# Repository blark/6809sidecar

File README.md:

# 6809sidecar

This board is untested and experimental.

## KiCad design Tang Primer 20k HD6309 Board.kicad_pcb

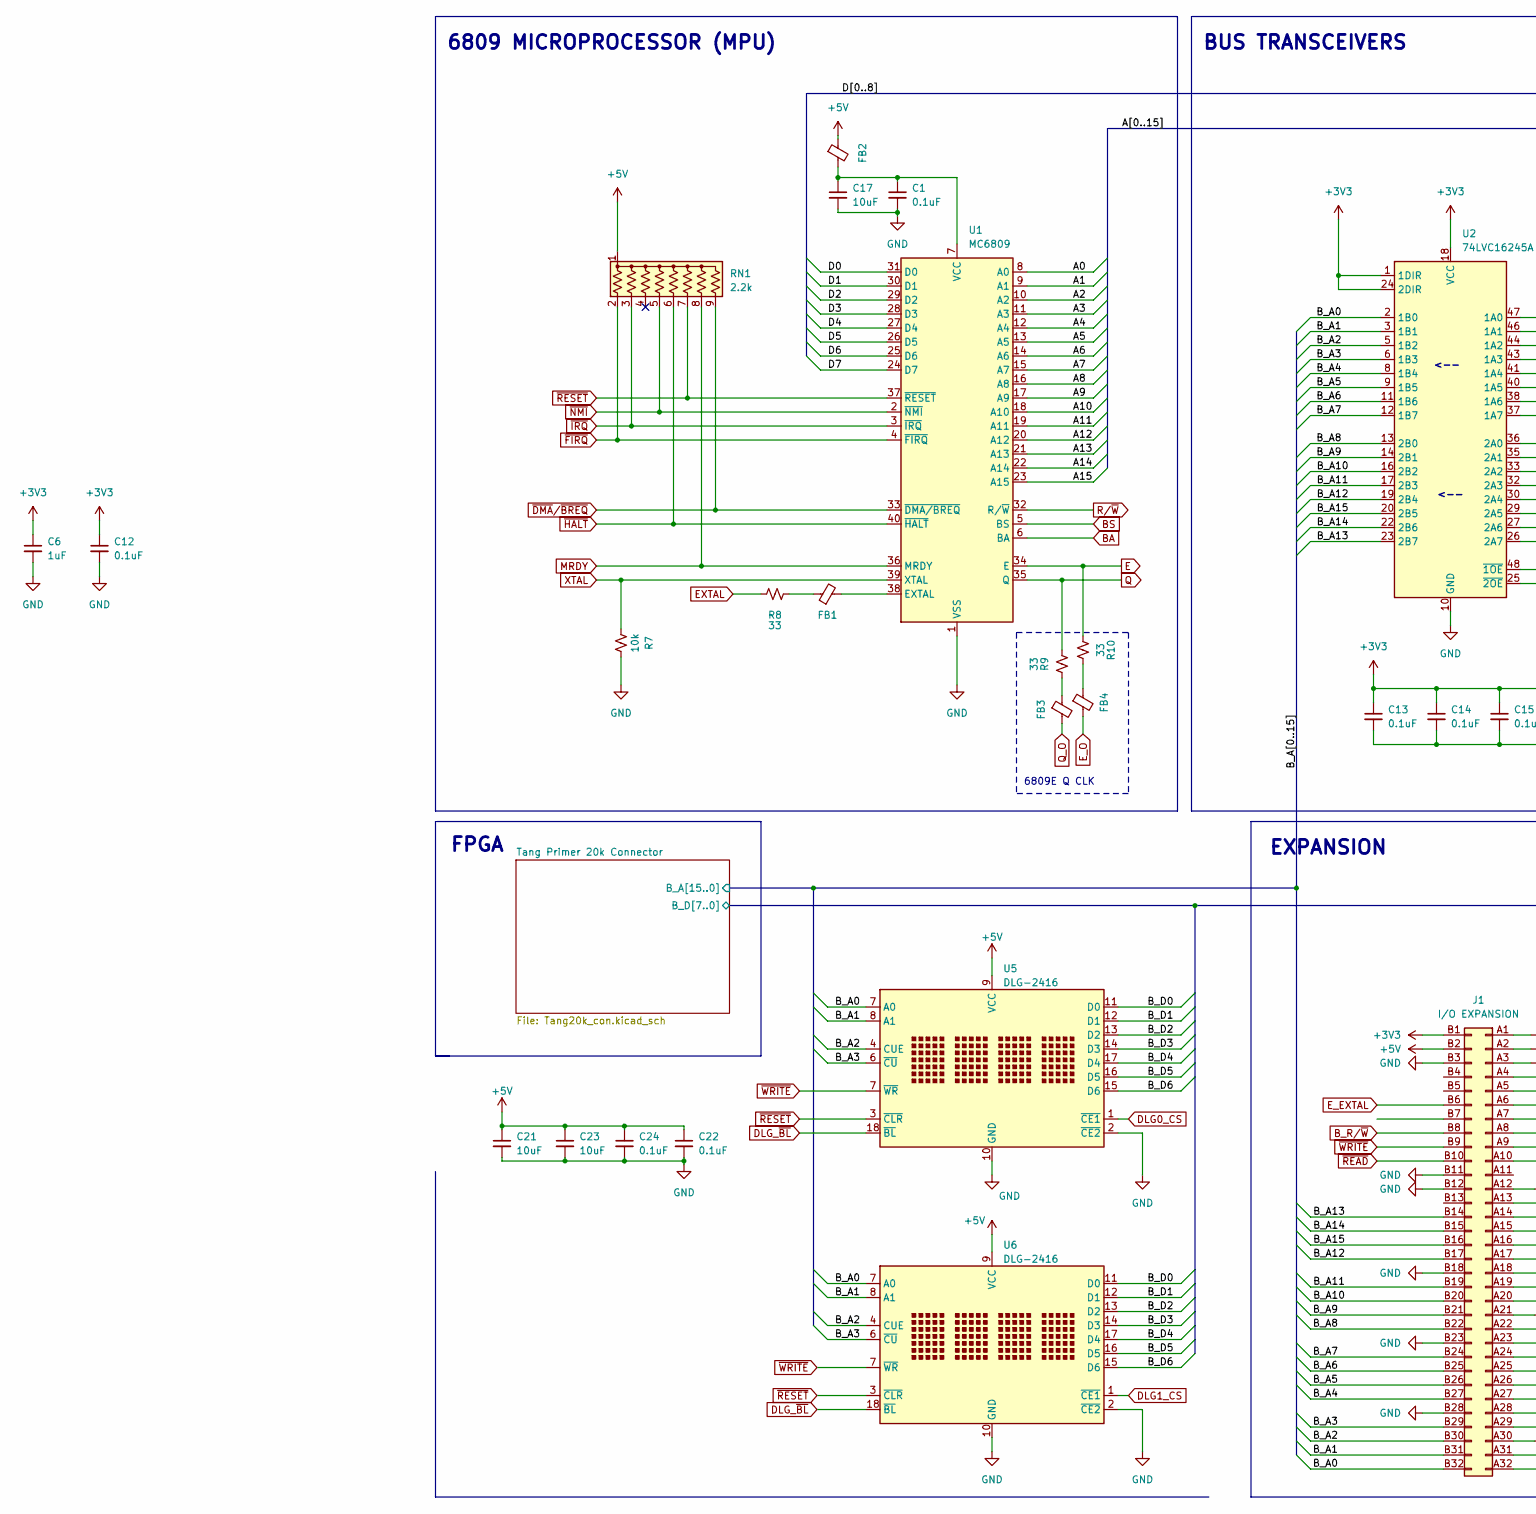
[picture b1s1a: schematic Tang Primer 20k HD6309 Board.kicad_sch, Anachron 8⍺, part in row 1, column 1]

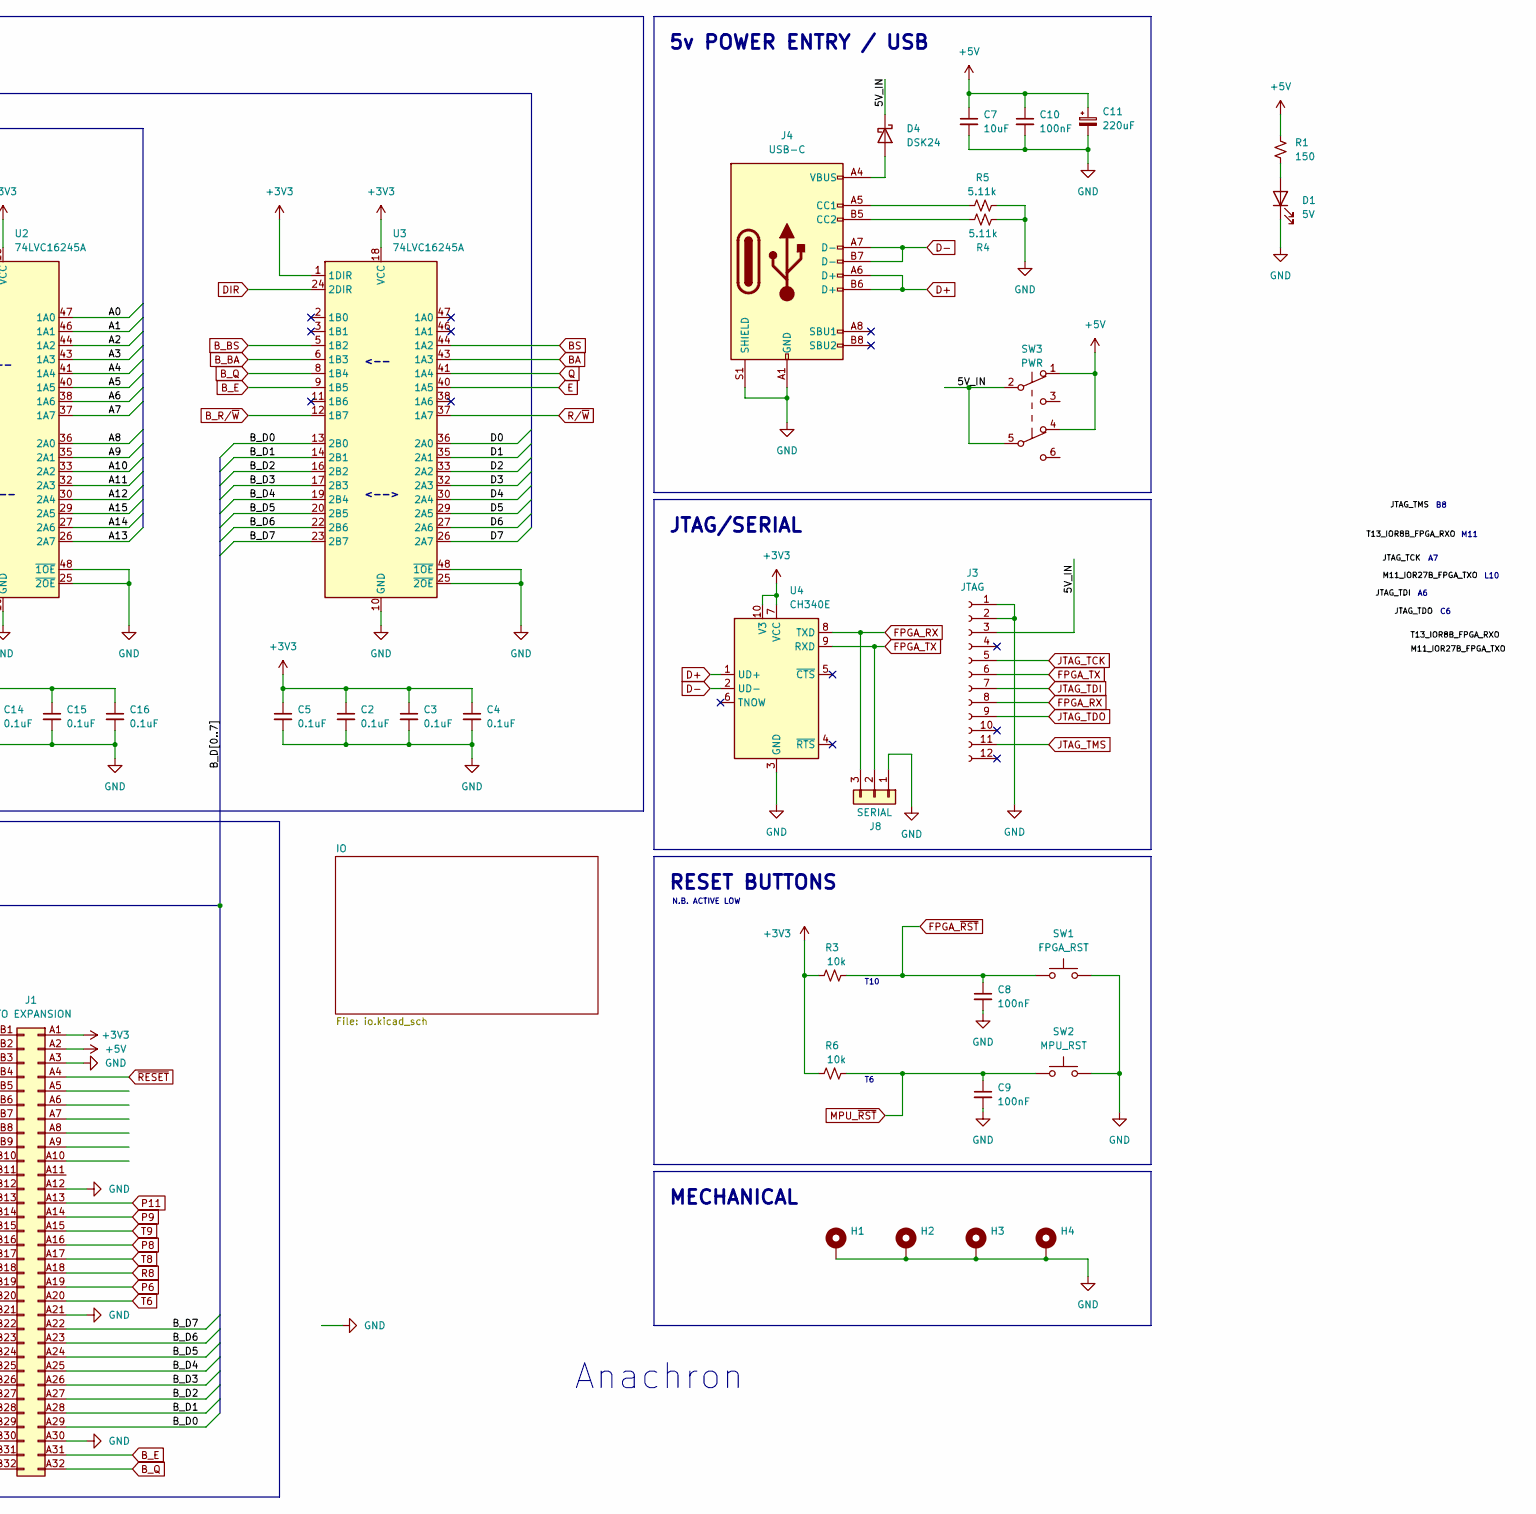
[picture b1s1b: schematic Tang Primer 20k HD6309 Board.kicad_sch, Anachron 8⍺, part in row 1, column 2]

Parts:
C1, C2, C3, C4, C5, C12, C13, C14, C15, C16, C22, C24: 0.1uF; C_0603_1608Metric_Pad1.08x0.95mm_HandSolder
C6: 1uF; C_0603_1608Metric_Pad1.08x0.95mm_HandSolder
C7: 10uF; C_0805_2012Metric
C8, C9, C10: 100nF; C_0603_1608Metric_Pad1.08x0.95mm_HandSolder
C11: 220uF; CP_Elec_6.3x7.7
C17, C21, C23: 10uF; C_0603_1608Metric_Pad1.08x0.95mm_HandSolder
D1: 5V; LED_0603_1608Metric_Pad1.05x0.95mm_HandSolder
D4: DSK24; C_0603_1608Metric_Pad1.08x0.95mm_HandSolder
FB1, FB3, FB4: UPZ1005D121-1R3TF
FB2: MPZ1608S101ATAH0; C_0603_1608Metric_Pad1.08x0.95mm_HandSolder
H1, H2, H3, H4: MountingHole_Pad; MountingHole_3.2mm_M3_Pad_Via
J1: I/O EXPANSION; BUS_PCIexpress_x4
J3: JTAG; IDC-Header_2x06_P2.54mm_Vertical
J4: USB-C; USB_C_Receptacle_HRO_TYPE-C-31-M-12
J8: SERIAL; PinHeader_1x03_P2.54mm_Vertical
R1: 150; R_0603_1608Metric_Pad0.98x0.95mm_HandSolder
R3, R6, R7: 10k; R_0603_1608Metric_Pad0.98x0.95mm_HandSolder
R4, R5: 5.11k; R_0603_1608Metric_Pad0.98x0.95mm_HandSolder
R8, R9, R10: 33; R_0603_1608Metric_Pad0.98x0.95mm_HandSolder
RN1: 2.2k; R_Array_Convex_5x0603
SW1, SW2: PTS636SK25SMTRLFS; SW_SPST_CK_RS282G05A3
SW3: PWR; 2UD1T1A1M2RES
U1: MC6809; 3M_Textool_240-1288-00-0602J_2x20_P2.54mm
U2, U3: 74LVC16245A; TSSOP-48_6.1x12.5mm_P0.5mm
U4: CH340E; MSOP-10_3x3mm_P0.5mm
U5, U6: DLG-2416; DIP-18_W15.24mm_LongPads

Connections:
/5V_IN: D4.1 (K), J3.3, SW3.2 (B), SW3.5 (B)
/A0: U1.8 (A0), U2.47 (1A0)
/A1: U1.9 (A1), U2.46 (1A1)
/A2: U1.10 (A2), U2.44 (1A2)
/A3: U1.11 (A3), U2.43 (1A3)
/A4: U1.12 (A4), U2.41 (1A4)
/A5: U1.13 (A5), U2.40 (1A5)
/A6: U1.14 (A6), U2.38 (1A6)
/A7: U1.15 (A7), U2.37 (1A7)
/A8: U1.16 (A8), U2.36 (2A0)
/A9: U1.17 (A9), U2.35 (2A1)
/A10: U1.18 (A10), U2.33 (2A2)
/A11: U1.19 (A11), U2.32 (2A3)
/A12: U1.20 (A12), U2.30 (2A4)
/A13: U1.21 (A13), U2.26 (2A7)
/A14: U1.22 (A14), U2.27 (2A6)
/A15: U1.23 (A15), U2.29 (2A5)
/B_A1: J1.B31 (Pin_b31), U2.3 (1B1), U5.8 (A1), U6.8 (A1); also elsewhere on the board
/B_A2: J1.B30 (Pin_b30), U2.5 (1B2), U5.4 (CUE), U6.4 (CUE); also elsewhere on the board
/B_A3: J1.B29 (Pin_b29), U2.6 (1B3), U5.6 (~CU), U6.6 (~CU); also elsewhere on the board
/B_A4: J1.B27 (Pin_b27), U2.8 (1B4); also elsewhere on the board
/B_A5: J1.B26 (Pin_b26), U2.9 (1B5); also elsewhere on the board
/B_A6: J1.B25 (Pin_b25), U2.11 (1B6); also elsewhere on the board
/B_A7: J1.B24 (Pin_b24), U2.12 (1B7); also elsewhere on the board
/B_A8: J1.B22 (Pin_b22), U2.13 (2B0); also elsewhere on the board
/B_A9: J1.B21 (Pin_b21), U2.14 (2B1); also elsewhere on the board
/B_A10: J1.B20 (Pin_b20), U2.16 (2B2); also elsewhere on the board
/B_A11: J1.B19 (Pin_b19), U2.17 (2B3); also elsewhere on the board
/B_A12: J1.B17 (Pin_b17), U2.19 (2B4); also elsewhere on the board
/B_A13: J1.B14 (Pin_b14), U2.23 (2B7); also elsewhere on the board
/B_A14: J1.B15 (Pin_b15), U2.22 (2B6); also elsewhere on the board
/B_A15: J1.B16 (Pin_b16), U2.20 (2B5); also elsewhere on the board
/B_D0: J1.A29 (Pin_a29), U3.13 (2B0), U5.11 (D0), U6.11 (D0); also elsewhere on the board
/B_D1: J1.A28 (Pin_a28), U3.14 (2B1), U5.12 (D1), U6.12 (D1); also elsewhere on the board
/B_D2: J1.A27 (Pin_a27), U3.16 (2B2), U5.13 (D2), U6.13 (D2); also elsewhere on the board
/B_D3: J1.A26 (Pin_a26), U3.17 (2B3), U5.14 (D3), U6.14 (D3); also elsewhere on the board
/B_D4: J1.A25 (Pin_a25), U3.19 (2B4), U5.17 (D4), U6.17 (D4); also elsewhere on the board
/B_D5: J1.A24 (Pin_a24), U3.20 (2B5), U5.16 (D5), U6.16 (D5); also elsewhere on the board
/B_D6: J1.A23 (Pin_a23), U3.22 (2B6), U5.15 (D6), U6.15 (D6); also elsewhere on the board
/B_D7: J1.A22 (Pin_a22), U3.23 (2B7); also elsewhere on the board
/D0: U1.31 (D0), U3.36 (2A0)
/D1: U1.30 (D1), U3.35 (2A1)
/D2: U1.29 (D2), U3.33 (2A2)
/D3: U1.28 (D3), U3.32 (2A3)
/D4: U1.27 (D4), U3.30 (2A4)
/D5: U1.26 (D5), U3.29 (2A5)
/D6: U1.25 (D6), U3.27 (2A6)
/D7: U1.24 (D7), U3.26 (2A7)
BA: U1.6 (BA), U3.43 (1A3)
BS: U1.5 (BS), U3.44 (1A2)
B_BA: U3.6 (1B3); also elsewhere on the board
B_BS: U3.5 (1B2); also elsewhere on the board
B_E: J1.A31 (Pin_a31), U3.9 (1B5); also elsewhere on the board
B_Q: J1.A32 (Pin_a32), U3.8 (1B4); also elsewhere on the board
B_R/~W: J1.B8 (Pin_b8), U3.12 (1B7); also elsewhere on the board
D+: J4.A6 (D+), J4.B6 (D+), U4.1 (UD+)
D-: J4.A7 (D-), J4.B7 (D-), U4.2 (UD-)
DIR: U3.24 (2DIR); also elsewhere on the board
DLG0_CS: U5.1 (~CE1); also elsewhere on the board
DLG1_CS: U6.1 (~CE1); also elsewhere on the board
DLG_~BL: U5.18 (~BL), U6.18 (~BL); also elsewhere on the board
E: R10.2, U1.34 (E), U3.40 (1A5)
EXTAL: R8.2; also elsewhere on the board
E_EXTAL: J1.B6 (Pin_b6); also elsewhere on the board
FPGA_RX: J3.8, J8.3, U4.8 (TXD); also elsewhere on the board
FPGA_TX: J3.6, J8.2, U4.9 (RXD); also elsewhere on the board
FPGA_~RST: C8.1, R3.2, SW1.1; also elsewhere on the board
JTAG_TCK: J3.5; also elsewhere on the board
JTAG_TDI: J3.7; also elsewhere on the board
JTAG_TDO: J3.9; also elsewhere on the board
JTAG_TMS: J3.11; also elsewhere on the board
MPU_~RST: C9.1, R6.2, SW2.1; also elsewhere on the board
MRDY: RN1.8 (R7), U1.36 (MRDY)
unnamed: D1.2 (A), R1.2
unnamed: D4.2 (A), J4.A4 (VBUS), J4.A9 (VBUS), J4.B4 (VBUS), J4.B9 (VBUS)
unnamed: FB1.1, R8.1
unnamed: FB3.1, R9.1
unnamed: FB4.1, R10.1
unnamed: J4.A5 (CC1), R5.1
unnamed: J4.B5 (CC2), R4.1
unnamed: FB1.2, U1.38 (EXTAL)
unnamed: C1.1, C17.1, FB2.2, U1.7 (VCC)
P6: J1.A19 (Pin_a19); also elsewhere on the board
P8: J1.A16 (Pin_a16); also elsewhere on the board
P9: J1.A14 (Pin_a14); also elsewhere on the board
P11: J1.A13 (Pin_a13); also elsewhere on the board
Q: R9.2, U1.35 (Q), U3.41 (1A4)
R8: J1.A18 (Pin_a18); also elsewhere on the board
R/~W: U1.32 (R/~W), U3.37 (1A7)
T6: J1.A20 (Pin_a20); also elsewhere on the board
T8: J1.A17 (Pin_a17); also elsewhere on the board
T9: J1.A15 (Pin_a15); also elsewhere on the board
XTAL: R7.2, U1.39 (XTAL)
~DMA/~BREQ: RN1.9 (R8), U1.33 (~DMA/BREQ)
~FIRQ: RN1.2 (R1), U1.4 (~FIRQ)
~HALT: RN1.6 (R5), U1.40 (~HALT); also elsewhere on the board
~IRQ: RN1.3 (R2), U1.3 (~IRQ)
~NMI: RN1.5 (R4), U1.2 (~NMI)
~READ: J1.B10 (Pin_b10); also elsewhere on the board
~RESET: J1.A4 (Pin_a4), RN1.7 (R6), U1.37 (~RESET), U5.3 (~CLR), U6.3 (~CLR); also elsewhere on the board

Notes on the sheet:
M11
BUS TRANSCEIVERS
6809 MICROPROCESSOR (MPU)
MECHANICAL
5v POWER ENTRY / USB
L10
N.B. ACTIVE LOW
<--
T10
RESET BUTTONS
EXPANSION
Anachron
<-->
JTAG/SERIAL
6809E Q CLK
FPGA

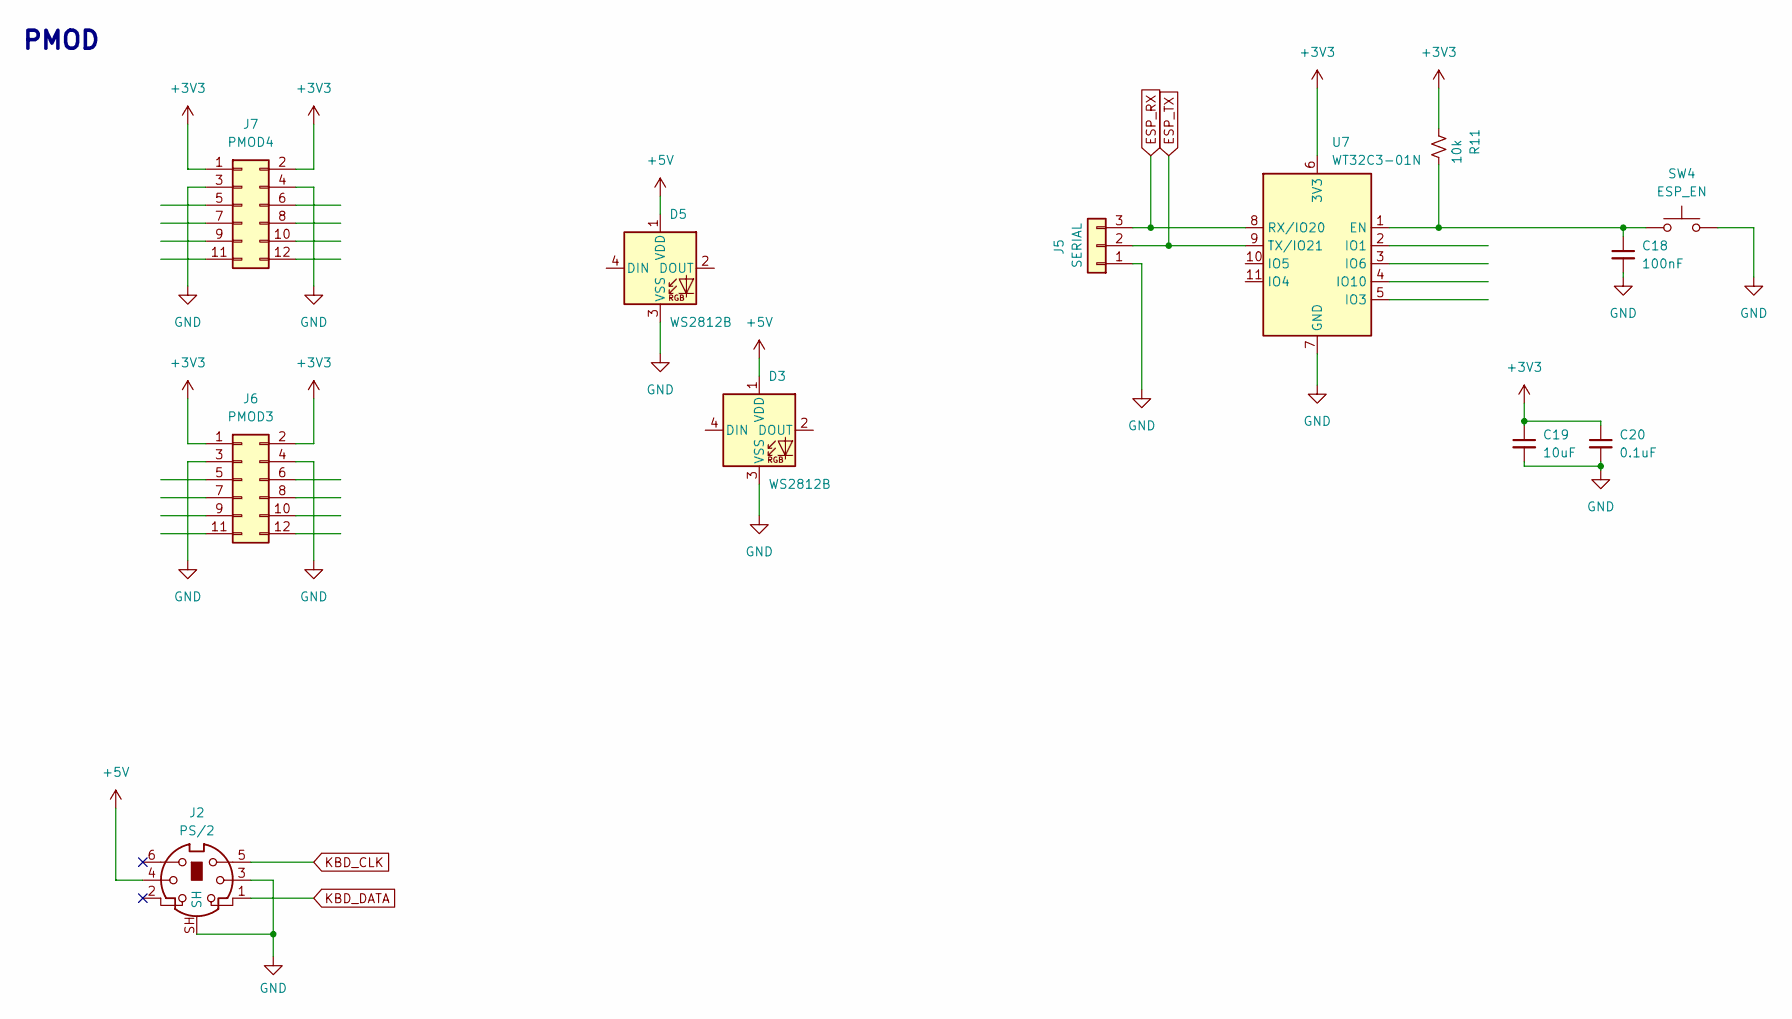
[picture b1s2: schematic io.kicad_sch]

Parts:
C18: 100nF; C_0603_1608Metric_Pad1.08x0.95mm_HandSolder
C19: 10uF; C_0603_1608Metric_Pad1.08x0.95mm_HandSolder
C20: 0.1uF; C_0603_1608Metric_Pad1.08x0.95mm_HandSolder
D3, D5: WS2812B; LED_WS2812B_PLCC4_5.0x5.0mm_P3.2mm
J2: PS/2; DS1093-01
J5: SERIAL; PinHeader_1x03_P2.54mm_Vertical
J6: PMOD3; PinSocket_2x06_P2.54mm_Horizontal
J7: PMOD4; PinSocket_2x06_P2.54mm_Horizontal
R11: 10k; R_0603_1608Metric_Pad0.98x0.95mm_HandSolder
SW4: PTS636SK25SMTRLFS; SW_SPST_CK_RS282G05A3
U7: WT32C3-01N; WT32C3

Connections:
ESP_RX: J5.3, U7.8 (RX/IO20)
ESP_TX: J5.2, U7.9 (TX/IO21)
KBD_CLK: J2.5
KBD_DATA: J2.1

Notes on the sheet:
PMOD

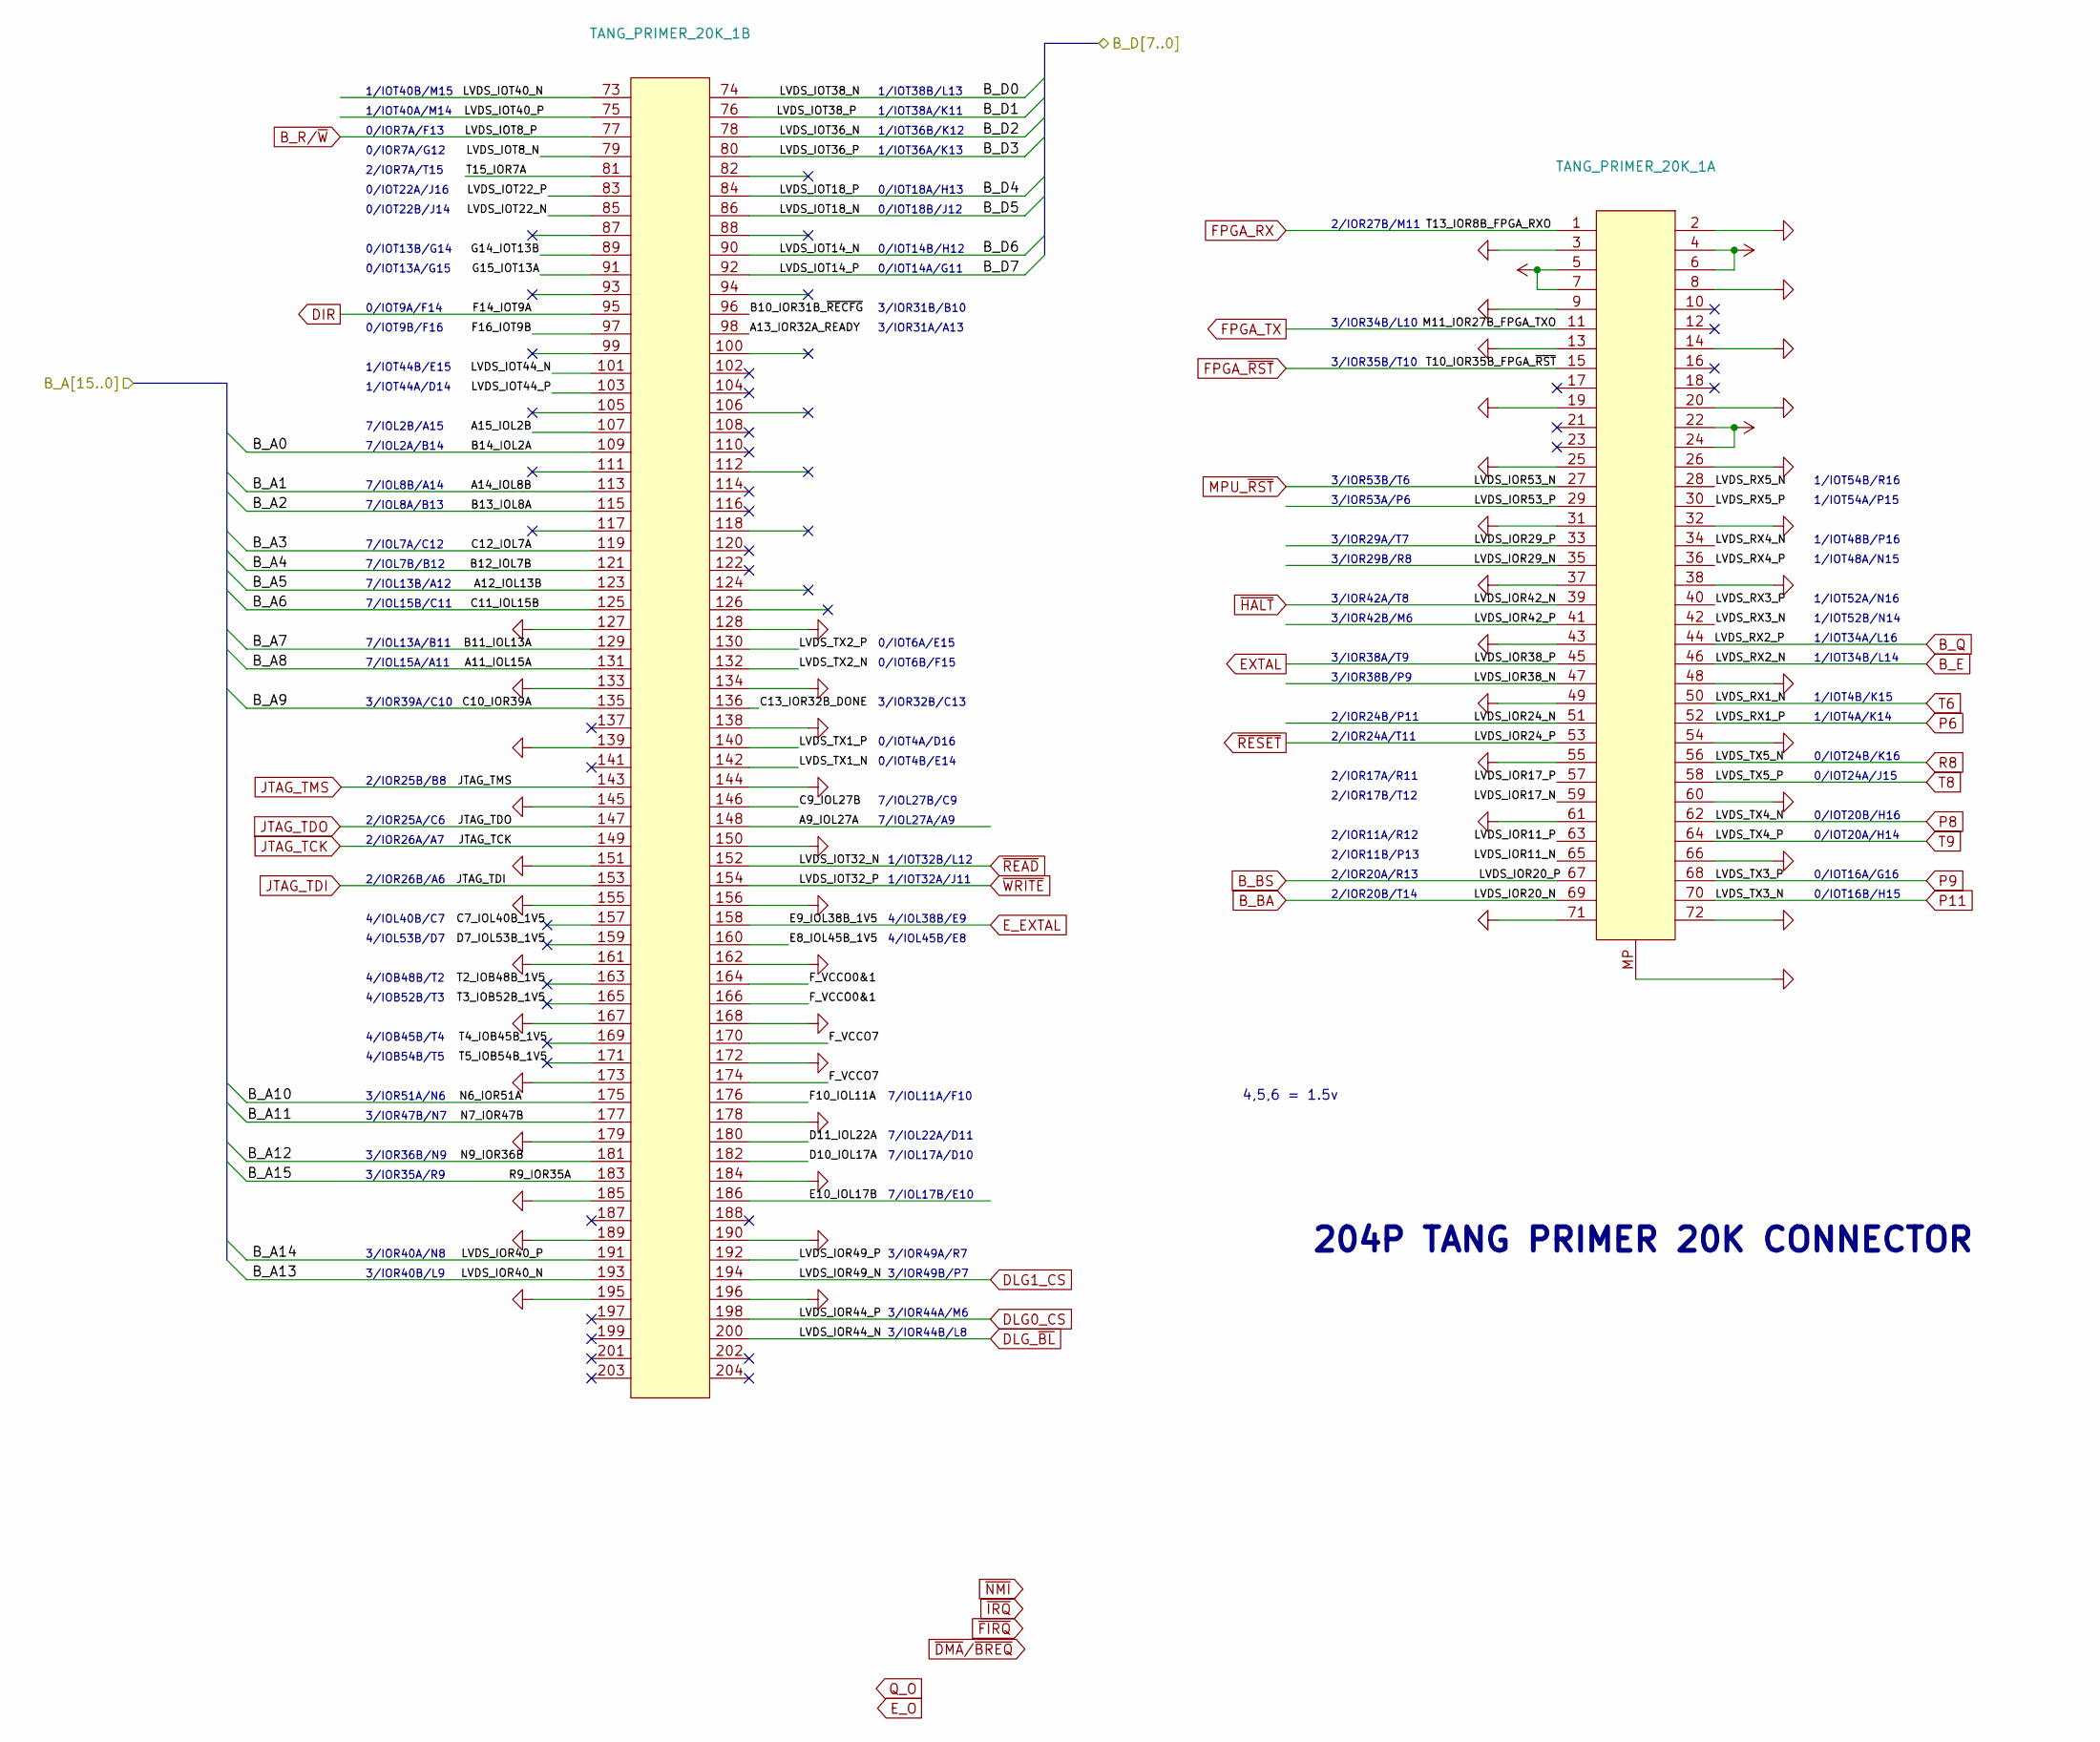
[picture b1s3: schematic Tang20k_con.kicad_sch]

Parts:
TANG_PRIMER_20K_1: DDR3-SMD_0705F0BE40F

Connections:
/B_A1: TANG_PRIMER_20K_1.113; also elsewhere on the board
/B_A2: TANG_PRIMER_20K_1.115; also elsewhere on the board
/B_A3: TANG_PRIMER_20K_1.119; also elsewhere on the board
/B_A4: TANG_PRIMER_20K_1.121; also elsewhere on the board
/B_A5: TANG_PRIMER_20K_1.123; also elsewhere on the board
/B_A6: TANG_PRIMER_20K_1.125; also elsewhere on the board
/B_A7: TANG_PRIMER_20K_1.129; also elsewhere on the board
/B_A8: TANG_PRIMER_20K_1.131; also elsewhere on the board
/B_A9: TANG_PRIMER_20K_1.135; also elsewhere on the board
/B_A10: TANG_PRIMER_20K_1.175; also elsewhere on the board
/B_A11: TANG_PRIMER_20K_1.177; also elsewhere on the board
/B_A12: TANG_PRIMER_20K_1.181; also elsewhere on the board
/B_A13: TANG_PRIMER_20K_1.193; also elsewhere on the board
/B_A14: TANG_PRIMER_20K_1.191; also elsewhere on the board
/B_A15: TANG_PRIMER_20K_1.183; also elsewhere on the board
/B_D0: TANG_PRIMER_20K_1.74; also elsewhere on the board
/B_D1: TANG_PRIMER_20K_1.76; also elsewhere on the board
/B_D2: TANG_PRIMER_20K_1.78; also elsewhere on the board
/B_D3: TANG_PRIMER_20K_1.80; also elsewhere on the board
/B_D4: TANG_PRIMER_20K_1.84; also elsewhere on the board
/B_D5: TANG_PRIMER_20K_1.86; also elsewhere on the board
/B_D6: TANG_PRIMER_20K_1.90; also elsewhere on the board
/B_D7: TANG_PRIMER_20K_1.92; also elsewhere on the board
/Tang Primer 20k Connector/A9_IOL27A: TANG_PRIMER_20K_1.148
/Tang Primer 20k Connector/A13_IOR32A_READY: TANG_PRIMER_20K_1.98
/Tang Primer 20k Connector/A15_IOL2B: TANG_PRIMER_20K_1.107
/Tang Primer 20k Connector/B10_IOR31B_~RECFG: TANG_PRIMER_20K_1.96
/Tang Primer 20k Connector/C7_IOL40B_1V5: TANG_PRIMER_20K_1.157
/Tang Primer 20k Connector/C9_IOL27B: TANG_PRIMER_20K_1.146
/Tang Primer 20k Connector/C13_IOR32B_DONE: TANG_PRIMER_20K_1.136
/Tang Primer 20k Connector/D7_IOL53B_1V5: TANG_PRIMER_20K_1.159
/Tang Primer 20k Connector/D10_IOL17A: TANG_PRIMER_20K_1.182
/Tang Primer 20k Connector/D11_IOL22A: TANG_PRIMER_20K_1.180
/Tang Primer 20k Connector/E8_IOL45B_1V5: TANG_PRIMER_20K_1.160
/Tang Primer 20k Connector/E10_IOL17B: TANG_PRIMER_20K_1.186
/Tang Primer 20k Connector/F10_IOL11A: TANG_PRIMER_20K_1.176
/Tang Primer 20k Connector/F16_IOT9B: TANG_PRIMER_20K_1.97
/Tang Primer 20k Connector/F_VCCO0&1: TANG_PRIMER_20K_1.164, TANG_PRIMER_20K_1.166
/Tang Primer 20k Connector/F_VCCO7: TANG_PRIMER_20K_1.170, TANG_PRIMER_20K_1.174
/Tang Primer 20k Connector/G14_IOT13B: TANG_PRIMER_20K_1.89
/Tang Primer 20k Connector/G15_IOT13A: TANG_PRIMER_20K_1.91
/Tang Primer 20k Connector/LVDS_IOR11_N: TANG_PRIMER_20K_1.65
/Tang Primer 20k Connector/LVDS_IOR11_P: TANG_PRIMER_20K_1.63
/Tang Primer 20k Connector/LVDS_IOR17_N: TANG_PRIMER_20K_1.59
/Tang Primer 20k Connector/LVDS_IOR17_P: TANG_PRIMER_20K_1.57
/Tang Primer 20k Connector/LVDS_IOR24_N: TANG_PRIMER_20K_1.51
/Tang Primer 20k Connector/LVDS_IOR29_N: TANG_PRIMER_20K_1.35
/Tang Primer 20k Connector/LVDS_IOR29_P: TANG_PRIMER_20K_1.33
/Tang Primer 20k Connector/LVDS_IOR38_N: TANG_PRIMER_20K_1.47
/Tang Primer 20k Connector/LVDS_IOR42_P: TANG_PRIMER_20K_1.41
/Tang Primer 20k Connector/LVDS_IOR49_P: TANG_PRIMER_20K_1.192
/Tang Primer 20k Connector/LVDS_IOR53_P: TANG_PRIMER_20K_1.29
/Tang Primer 20k Connector/LVDS_IOT8_N: TANG_PRIMER_20K_1.79
/Tang Primer 20k Connector/LVDS_IOT22_N: TANG_PRIMER_20K_1.85
/Tang Primer 20k Connector/LVDS_IOT22_P: TANG_PRIMER_20K_1.83
/Tang Primer 20k Connector/LVDS_IOT40_N: TANG_PRIMER_20K_1.73
/Tang Primer 20k Connector/LVDS_IOT40_P: TANG_PRIMER_20K_1.75
/Tang Primer 20k Connector/LVDS_IOT44_N: TANG_PRIMER_20K_1.101
/Tang Primer 20k Connector/LVDS_IOT44_P: TANG_PRIMER_20K_1.103
/Tang Primer 20k Connector/LVDS_RX3_N: TANG_PRIMER_20K_1.42
/Tang Primer 20k Connector/LVDS_RX3_P: TANG_PRIMER_20K_1.40
/Tang Primer 20k Connector/LVDS_RX4_N: TANG_PRIMER_20K_1.34
/Tang Primer 20k Connector/LVDS_RX4_P: TANG_PRIMER_20K_1.36
/Tang Primer 20k Connector/LVDS_RX5_N: TANG_PRIMER_20K_1.28
/Tang Primer 20k Connector/LVDS_RX5_P: TANG_PRIMER_20K_1.30
/Tang Primer 20k Connector/LVDS_TX1_N: TANG_PRIMER_20K_1.142
/Tang Primer 20k Connector/LVDS_TX1_P: TANG_PRIMER_20K_1.140
/Tang Primer 20k Connector/LVDS_TX2_N: TANG_PRIMER_20K_1.132
/Tang Primer 20k Connector/LVDS_TX2_P: TANG_PRIMER_20K_1.130
/Tang Primer 20k Connector/T2_IOB48B_1V5: TANG_PRIMER_20K_1.163
/Tang Primer 20k Connector/T3_IOB52B_1V5: TANG_PRIMER_20K_1.165
/Tang Primer 20k Connector/T4_IOB45B_1V5: TANG_PRIMER_20K_1.169
/Tang Primer 20k Connector/T5_IOB54B_1V5: TANG_PRIMER_20K_1.171
/Tang Primer 20k Connector/T15_IOR7A: TANG_PRIMER_20K_1.81
B_BA: TANG_PRIMER_20K_1.69; also elsewhere on the board
B_BS: TANG_PRIMER_20K_1.67; also elsewhere on the board
B_E: TANG_PRIMER_20K_1.46; also elsewhere on the board
B_Q: TANG_PRIMER_20K_1.44; also elsewhere on the board
B_R/~W: TANG_PRIMER_20K_1.77; also elsewhere on the board
DIR: TANG_PRIMER_20K_1.95; also elsewhere on the board
DLG0_CS: TANG_PRIMER_20K_1.198; also elsewhere on the board
DLG1_CS: TANG_PRIMER_20K_1.194; also elsewhere on the board
DLG_~BL: TANG_PRIMER_20K_1.200; also elsewhere on the board
EXTAL: TANG_PRIMER_20K_1.45; also elsewhere on the board
E_EXTAL: TANG_PRIMER_20K_1.158; also elsewhere on the board
FPGA_RX: TANG_PRIMER_20K_1.1; also elsewhere on the board
FPGA_TX: TANG_PRIMER_20K_1.11; also elsewhere on the board
FPGA_~RST: TANG_PRIMER_20K_1.15; also elsewhere on the board
JTAG_TCK: TANG_PRIMER_20K_1.149; also elsewhere on the board
JTAG_TDI: TANG_PRIMER_20K_1.153; also elsewhere on the board
JTAG_TDO: TANG_PRIMER_20K_1.147; also elsewhere on the board
JTAG_TMS: TANG_PRIMER_20K_1.143; also elsewhere on the board
MPU_~RST: TANG_PRIMER_20K_1.27; also elsewhere on the board
P6: TANG_PRIMER_20K_1.52; also elsewhere on the board
P8: TANG_PRIMER_20K_1.62; also elsewhere on the board
P9: TANG_PRIMER_20K_1.68; also elsewhere on the board
P11: TANG_PRIMER_20K_1.70; also elsewhere on the board
R8: TANG_PRIMER_20K_1.56; also elsewhere on the board
T6: TANG_PRIMER_20K_1.50; also elsewhere on the board
T8: TANG_PRIMER_20K_1.58; also elsewhere on the board
T9: TANG_PRIMER_20K_1.64; also elsewhere on the board
~HALT: TANG_PRIMER_20K_1.39; also elsewhere on the board
~READ: TANG_PRIMER_20K_1.152; also elsewhere on the board
~RESET: TANG_PRIMER_20K_1.53; also elsewhere on the board

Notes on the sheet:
7/IOL7A/C12
3/IOR49A/R7
0/IOT24A/J15
3/IOR34B/L10
7/IOL22A/D11
4/IOB48B/T2
4/IOL45B/E8
3/IOR36B/N9
2/IOR11B/P13
1/IOT34A/L16
3/IOR51A/N6
1/IOT34B/L14
4,5,6 = 1.5v
7/IOL2B/A15
0/IOT18B/J12
0/IOT16A/G16
2/IOR17A/R11
0/IOR7A/F13
3/IOR40A/N8
4/IOB52B/T3
7/IOL17B/E10
0/IOT16B/H15
2/IOR24A/T11
2/IOR7A/T15
2/IOR26B/A6
2/IOR25B/B8
4/IOL38B/E9
0/IOT18A/H13
0/IOT13A/G15
3/IOR35B/T10
0/IOT13B/G14
2/IOR20A/R13
1/IOT32B/L12
7/IOL17A/D10
0/IOR7A/G12
0/IOT6A/E15
7/IOL13B/A12
1/IOT32A/J11
0/IOT24B/K16
3/IOR32B/C13

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
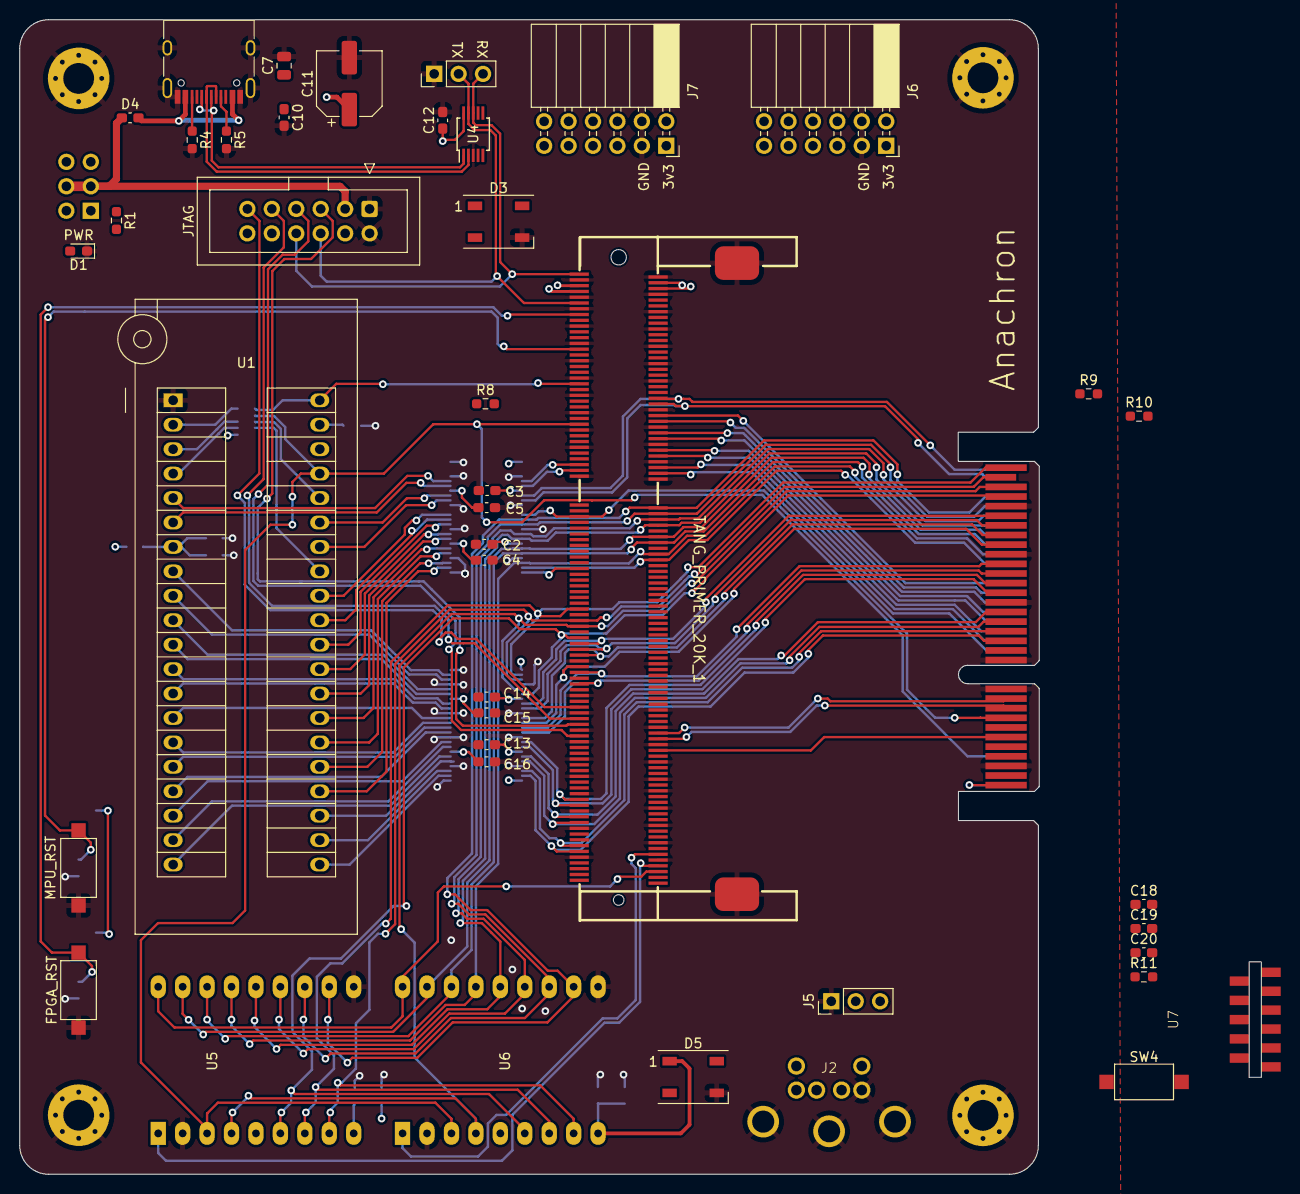
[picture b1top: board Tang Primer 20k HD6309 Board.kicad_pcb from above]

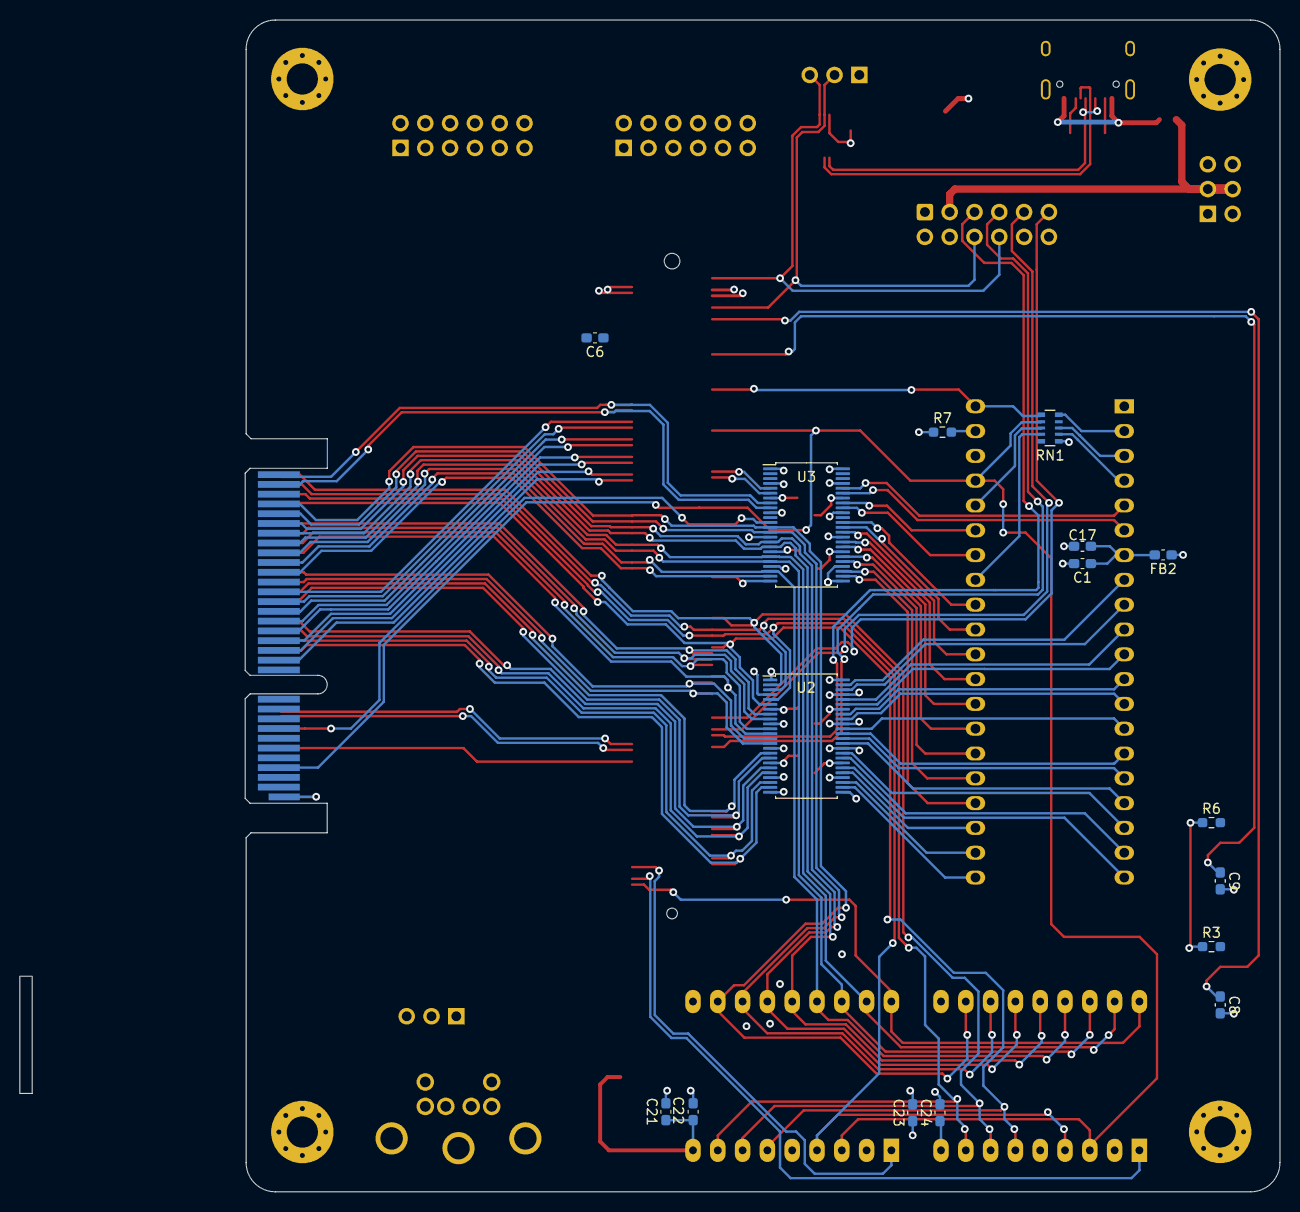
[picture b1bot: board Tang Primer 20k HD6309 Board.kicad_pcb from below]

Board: 4 copper layers, 129.0 x 120.0 mm, 64 parts (16 on the bottom side), 106 nets.

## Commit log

2023-01-27 warning
